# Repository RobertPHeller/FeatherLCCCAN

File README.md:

# FeatherLCCCAN

This is a Feather Wing for ESP32 Feathers that contain a CAN tranceiver and 
RJ45 connectors that allow connecting an ESP32 Feather to a LCC network.  The
CAN is set up to use pin 11 for CAN_TX and pin 12 for CAN_RX.

Subdirectories:

- firmware Simple node, without the display, 4Meg partition table, stores node
  DB on Flash under SPIFFS
- firmware-display Complex node, with display, 8Meg partition table, stores 
  node DB on uSD card (assumes Adafruit 3.5" TFT w/Touch Screen V2.0, which
  includes a uSD card slot).
- DisplayCase FreeCAD code for a case for the version with display.

The firmware compiles with Espressif esp-idf (at least V 5.0) and uses Mike 
Dunston's OpenMRNIDF library.

I am using KiCAD 6.0.11 on a Raspberry Pi 5 running Debian 12.  Also I am using
FreeCAD .21.2 (aarch64 Appimage).

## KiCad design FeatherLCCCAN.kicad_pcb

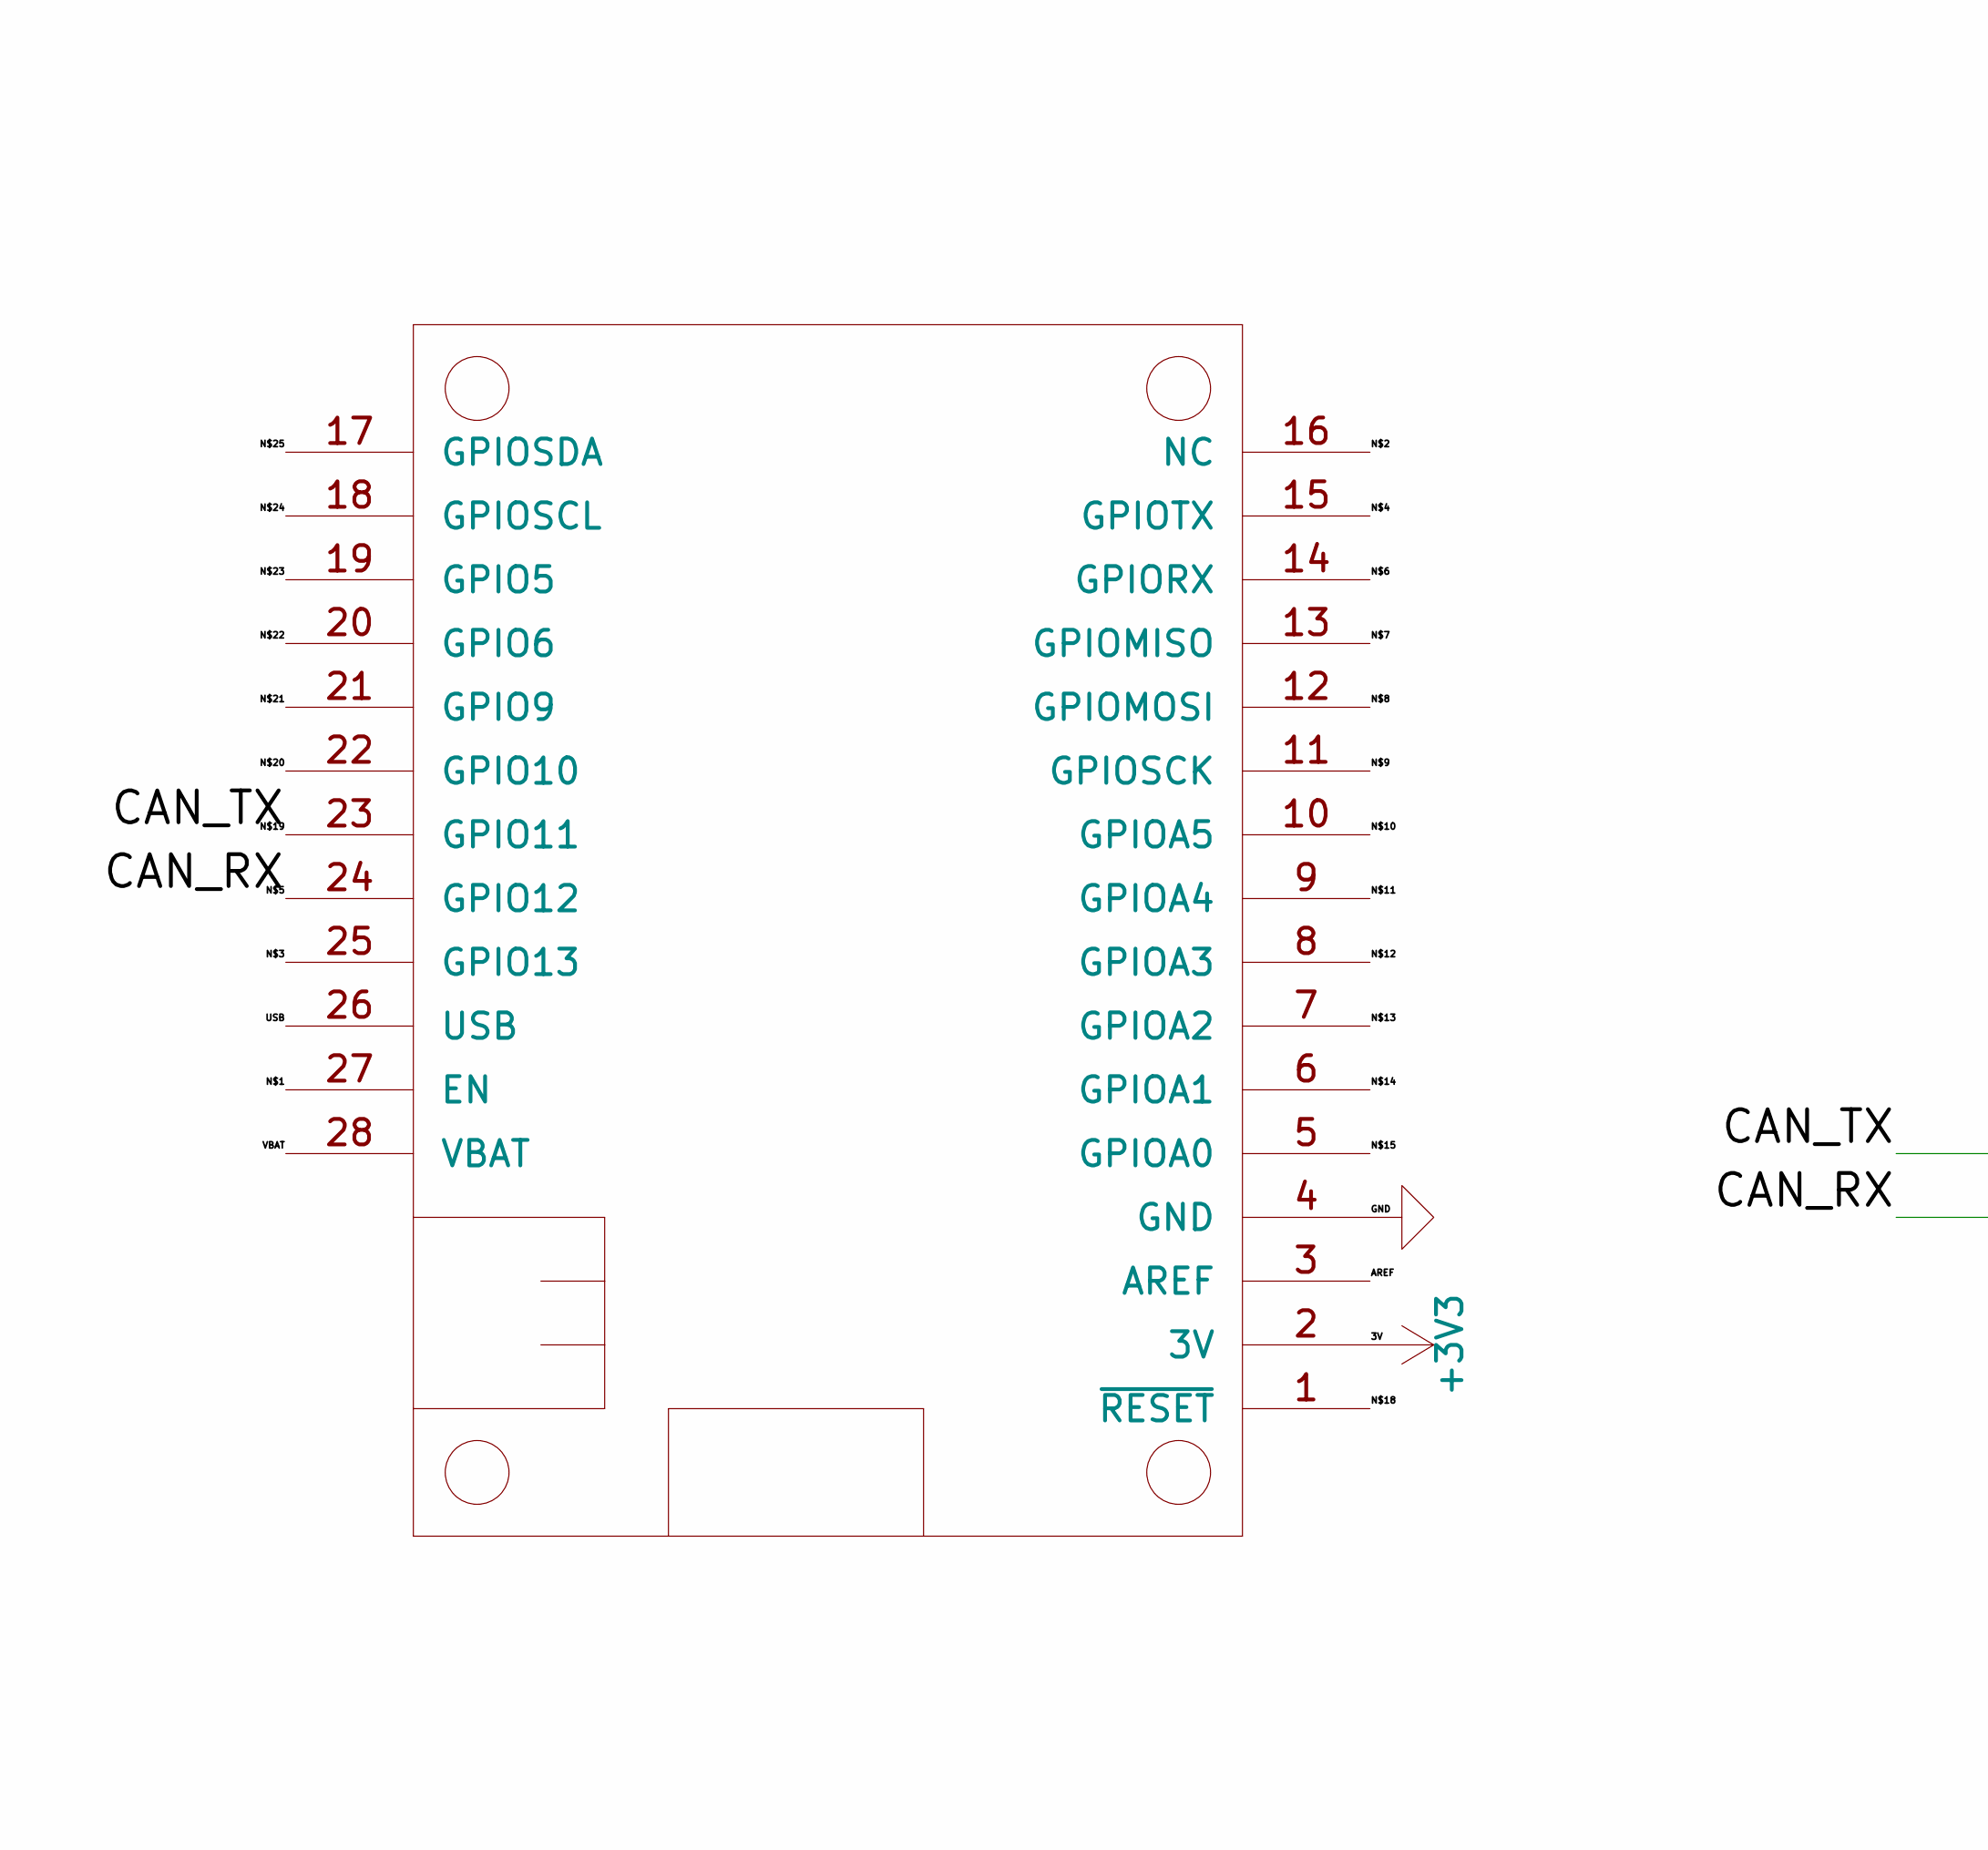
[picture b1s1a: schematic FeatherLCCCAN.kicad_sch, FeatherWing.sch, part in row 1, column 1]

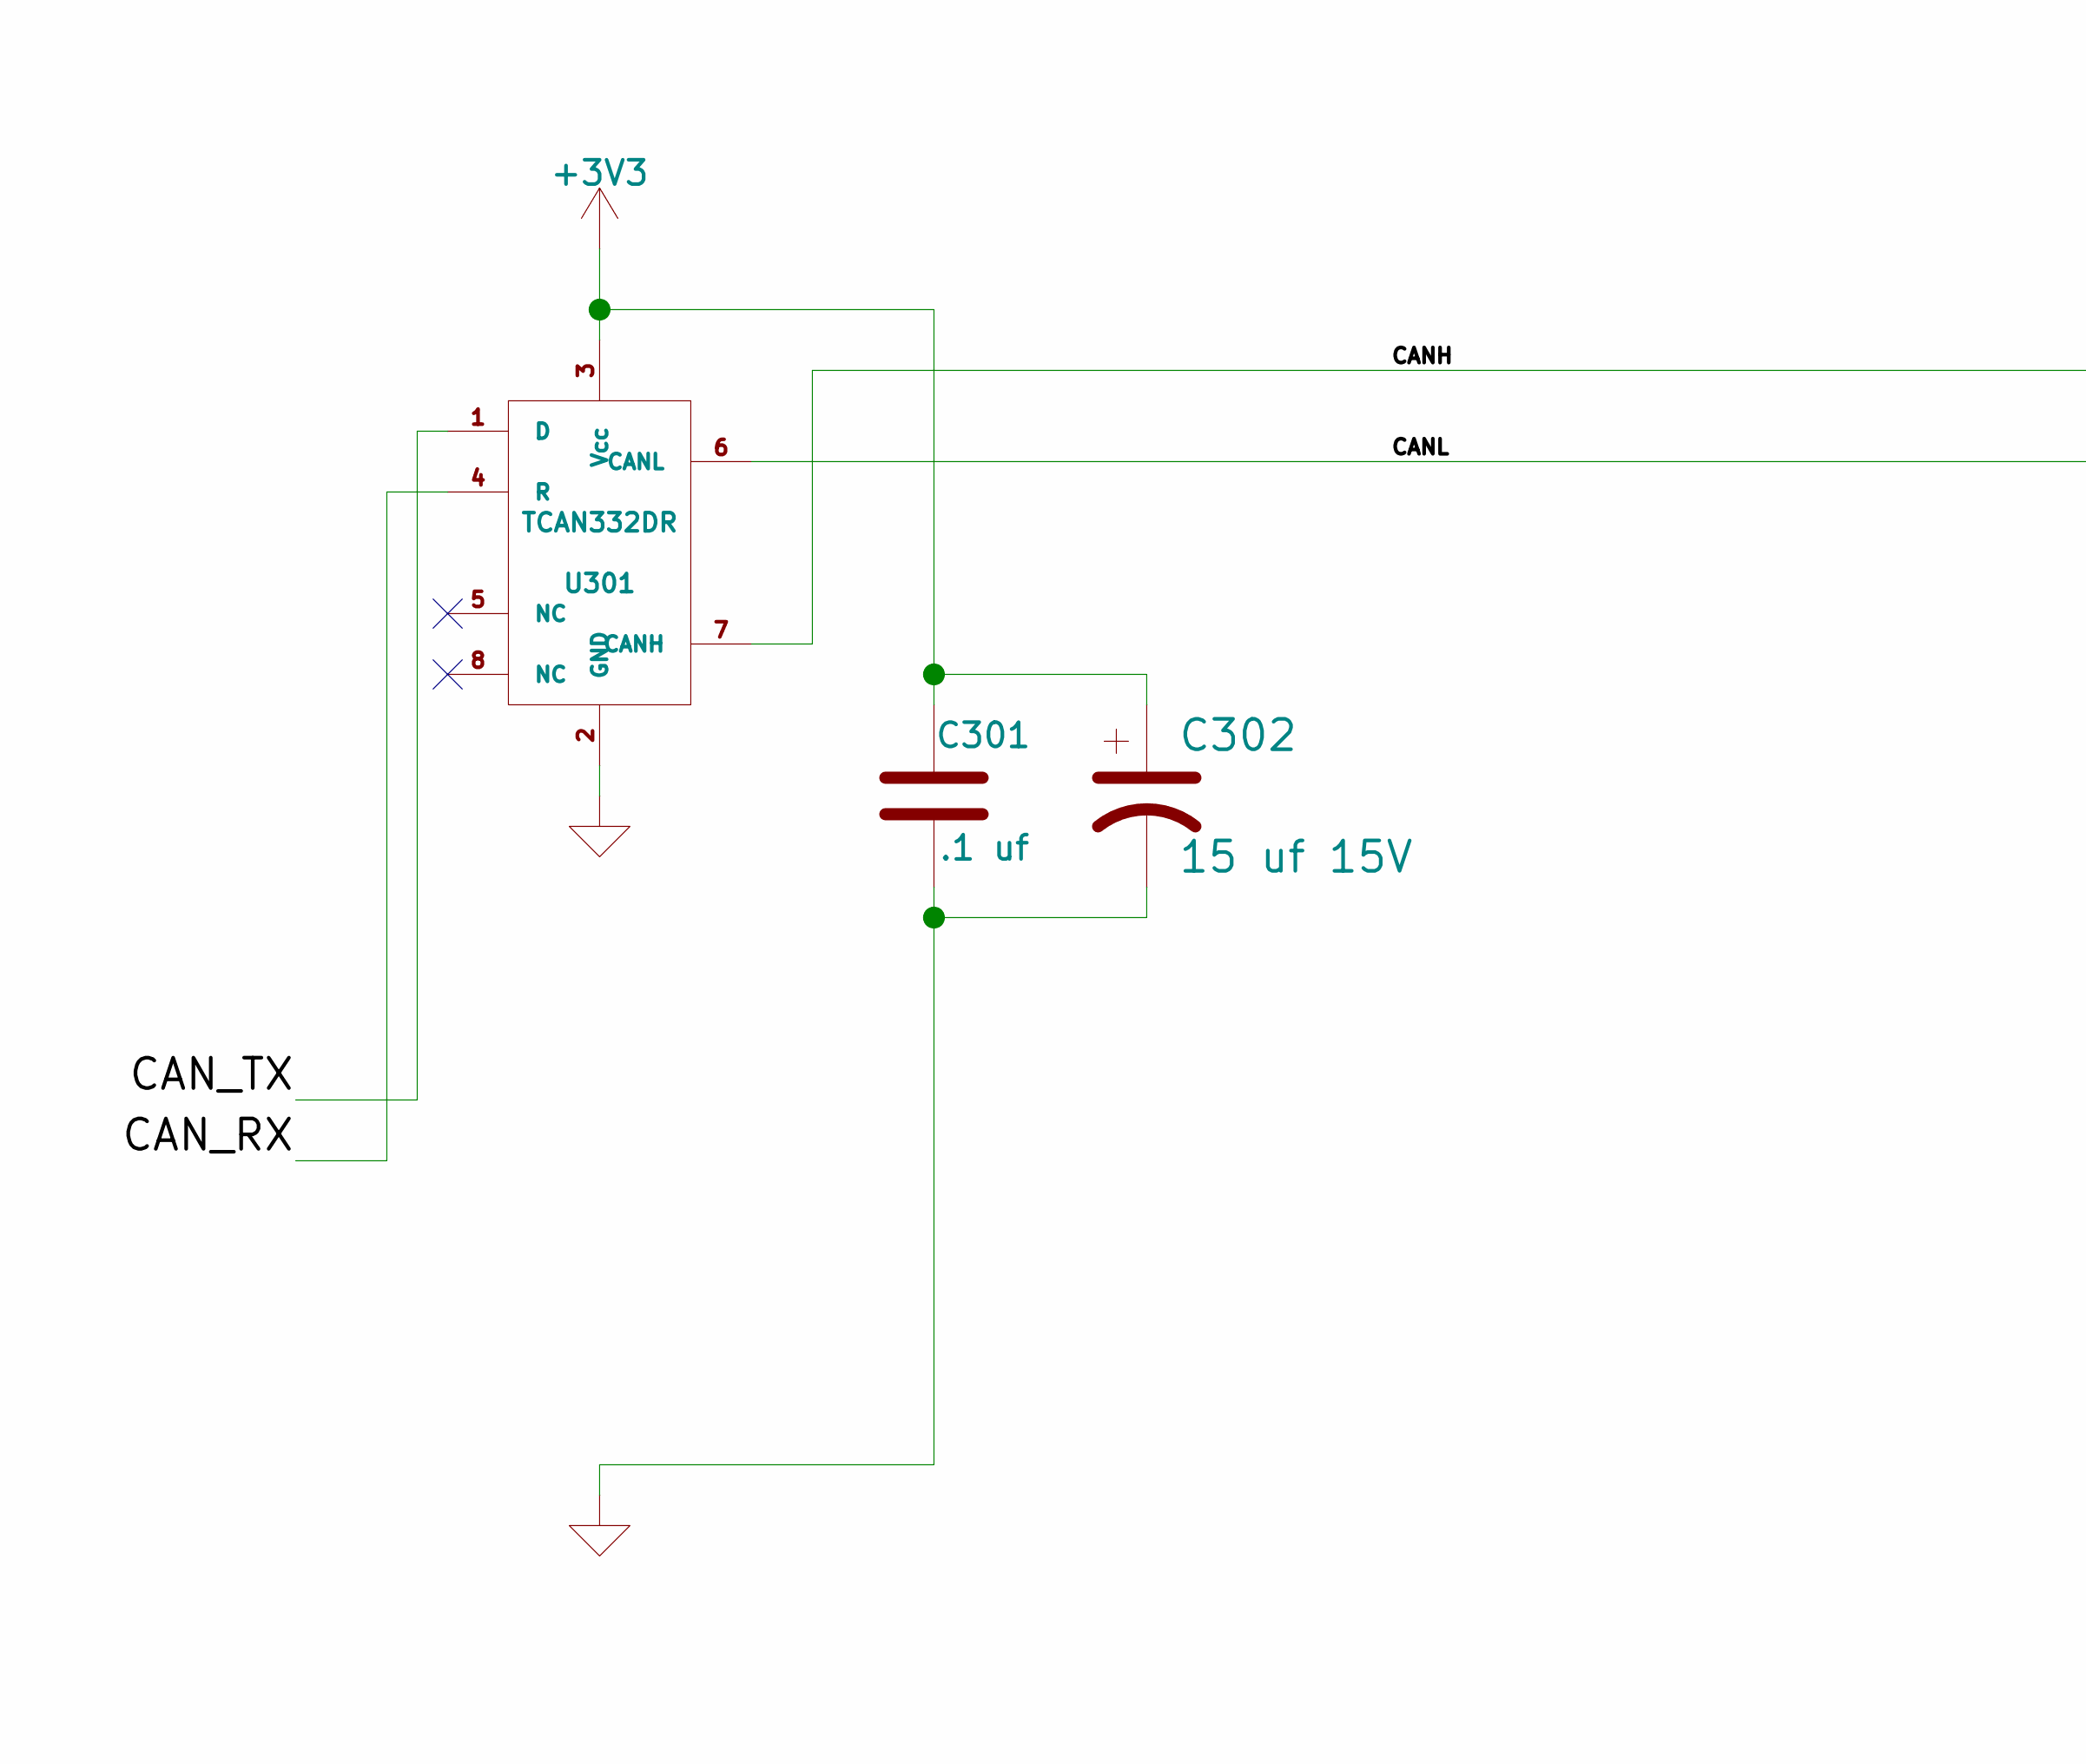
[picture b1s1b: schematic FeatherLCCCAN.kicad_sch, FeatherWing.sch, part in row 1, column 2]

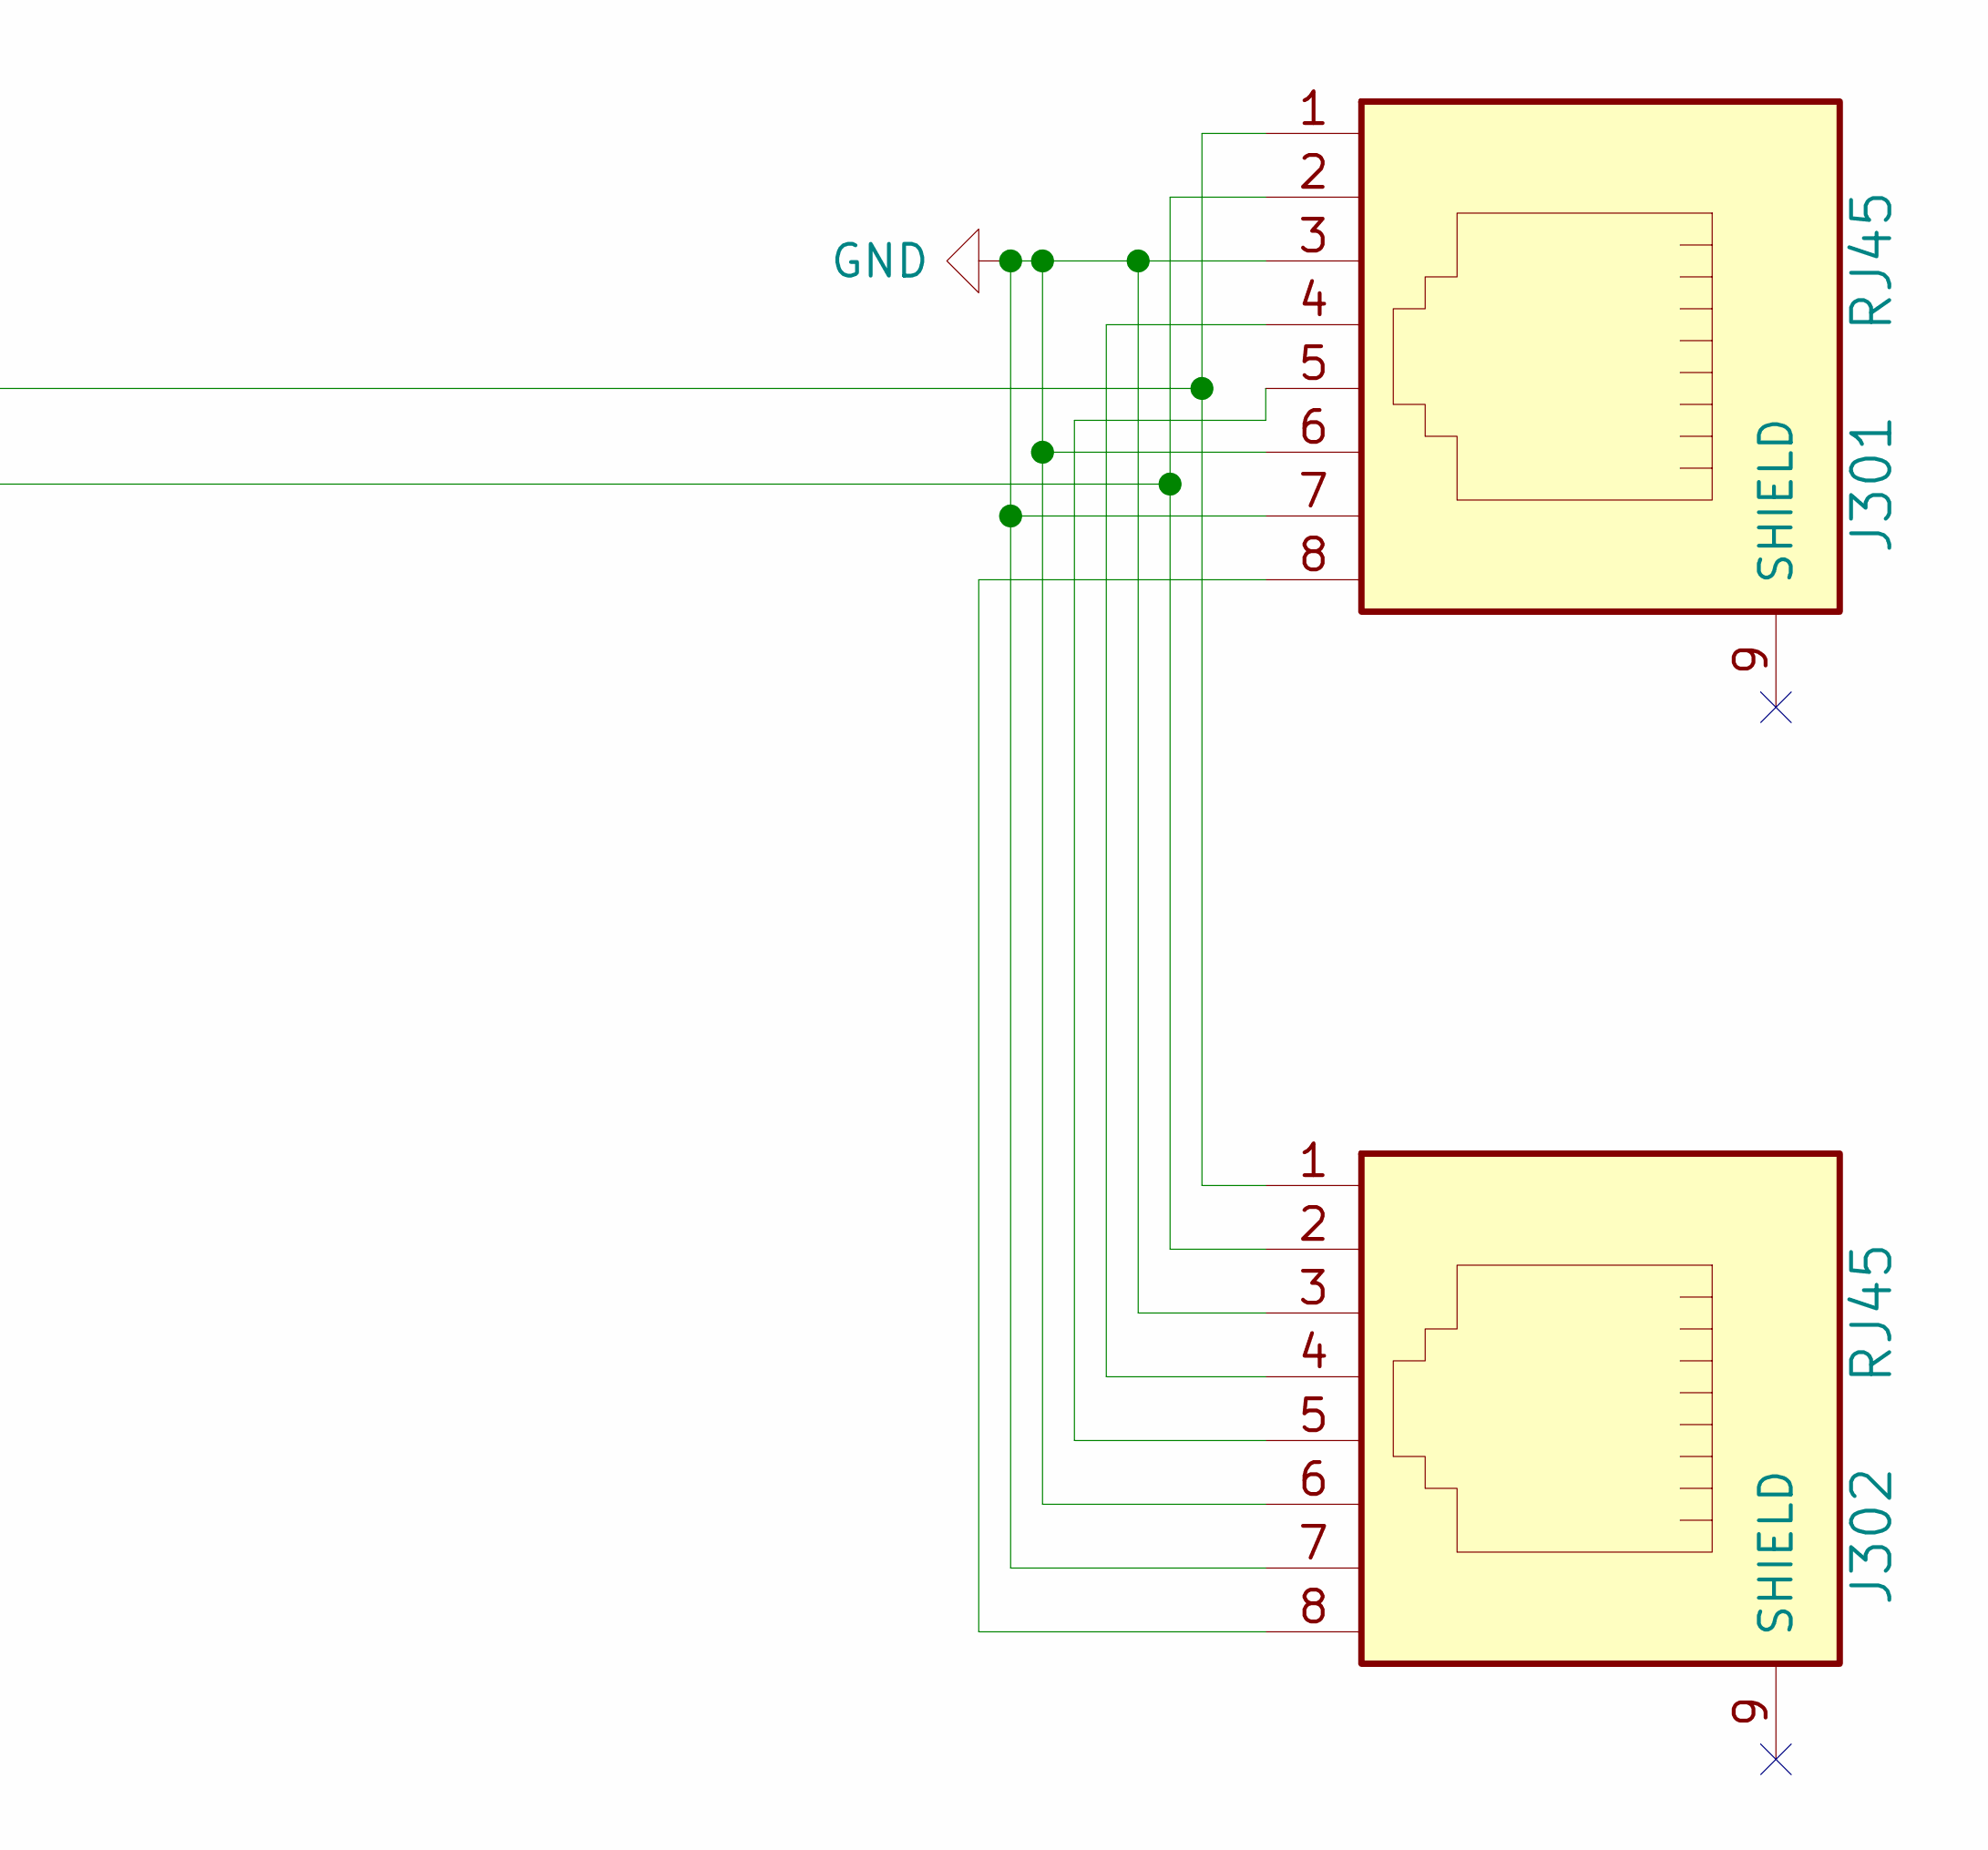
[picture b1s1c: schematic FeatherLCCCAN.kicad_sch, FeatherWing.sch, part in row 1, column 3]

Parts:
C301: .1 uf; C_0603_1608Metric; Mouser Part Number 710-885012206095
C302: 15 uf 15V; CP_Elec_4x5.7; Mouser Part Number 647-UUD1C150MCL
J301, J302: RJ45; RJ45_8N-S; Mouser Part Number 710-615008144221
MS1: FEATHERWING
U301: TCAN332DR; SOIC-8_3.9x4.9mm_P1.27mm; Mouser Part Number 595-TCAN332DR

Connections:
+3V3: C301.1, C302.1, MS1.2 (3V), U301.3 (Vcc)
/AREF: MS1.3 (AREF)
/CANH: J301.1, J302.1, U301.7 (CANH)
/CANL: J301.2, J302.2, U301.6 (CANL)
/CAN_RX: MS1.24 (GPIO12), U301.4 (R)
/CAN_TX: MS1.23 (GPIO11), U301.1 (D)
/N$1: MS1.27 (EN)
/N$2: MS1.16 (NC)
/N$3: MS1.25 (GPIO13)
/N$4: MS1.15 (GPIOTX)
/N$6: MS1.14 (GPIORX)
/N$7: MS1.13 (GPIOMISO)
/N$8: MS1.12 (GPIOMOSI)
/N$9: MS1.11 (GPIOSCK)
/N$10: MS1.10 (GPIOA5)
/N$11: MS1.9 (GPIOA4)
/N$12: MS1.8 (GPIOA3)
/N$13: MS1.7 (GPIOA2)
/N$14: MS1.6 (GPIOA1)
/N$15: MS1.5 (GPIOA0)
/N$18: MS1.1 (~RESET)
/N$20: MS1.22 (GPIO10)
/N$21: MS1.21 (GPIO9)
/N$22: MS1.20 (GPIO6)
/N$23: MS1.19 (GPIO5)
/N$24: MS1.18 (GPIOSCL)
/N$25: MS1.17 (GPIOSDA)
/USB: MS1.26 (USB)
/VBAT: MS1.28 (VBAT)
GND: C301.2, C302.2, J301.3, J301.6, J301.7, J302.3, J302.6, J302.7, MS1.4 (GND), U301.2 (GND)
unnamed: J301.4, J302.4
unnamed: J301.5, J302.5
unnamed: J301.8, J302.8

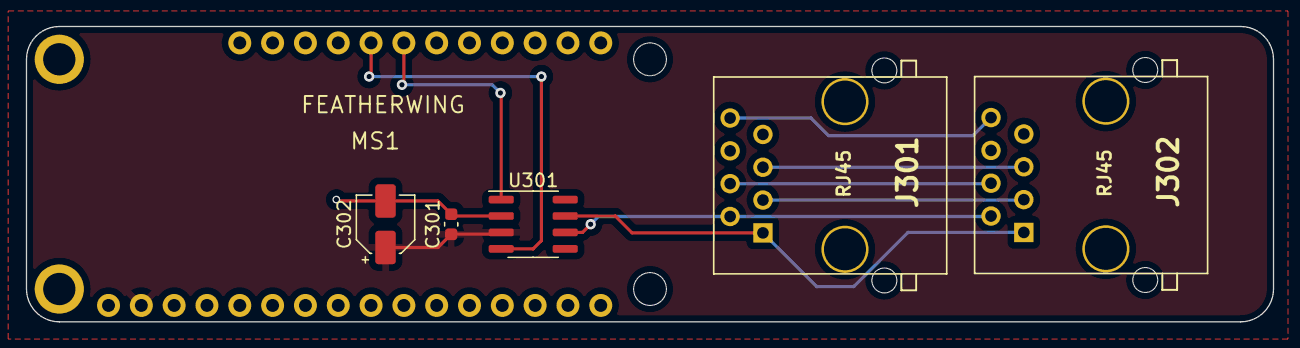
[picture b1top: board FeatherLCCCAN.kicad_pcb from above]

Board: 2 copper layers, 96.5 x 22.9 mm, 6 parts (0 on the bottom side), 9 nets.

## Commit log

2024-09-03 Completed LCC CAN Feather Wing.
2024-09-04 Build Infrastructure.
2024-09-04 Complete Boilerplate.
2024-09-04 Working on the firmware.
2024-09-05 Completed draft of firmware.
2024-09-05 Change CAN pins (allow for Adafruit 3.5" FeatherWing TFT & TouchScreen).
2024-09-06 Starting on Display version of the firmware.
2024-09-06 Started on case.
2024-09-07 Add mounting and pin holes.
2024-09-07 Rev B PCB.
2024-09-07 Added headers to feather.
2024-09-07 Complete LCC CAN Wing and Feather.
2024-09-08 Started on the box.
2024-09-08 Completed box.
2024-09-08 Completed lid.
2024-09-08 Finalize FeatherWing Display Board.
2024-09-08 Minor update.
2024-09-09 Complete porting of Arduino-ish Adafruit code to OpenMRNIDF / FreeRTOS code.
2024-09-09 Prepare NetworkHealthScan with accessors for use by the display code.
2024-09-10 Finish DisplayNetworkHealth.
2024-09-11 And STL export code.
2024-09-11 Add 3D view of the Rev B board.
2024-09-11 Update readme.
2024-09-11 Add 3D models for the connectors and create 3D image.
2024-09-12 Create LICENSE
2024-11-03 Build for a 4meg ESP32S3 Feather.
2025-01-21 Increase the stack sizes, update Makefile, add logging, prevent race condition.
2025-03-12 Add Plot directory.
2025-03-12 Working on NetworkHealthScan.
2025-05-07 Update part numbers.
2025-05-08 Add MPN property (for PCBWay plugin).
